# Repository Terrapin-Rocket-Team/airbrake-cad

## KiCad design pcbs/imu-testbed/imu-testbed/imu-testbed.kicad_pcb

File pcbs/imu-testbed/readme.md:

# IMU Testbed
This pcb was created with the goal of allowing us to test & validate different configurations for IMU's and barometers. It currently holds 2 LSM9DSLTR 9-axis IMUs and 1 LPS22HB barometer, and is controlled by a Teensy 4.1. On the back of the pcb are solder jumpers for configuring the address of the accelerometer, gyroscope, and magnitometer for each IMU. On the front are 2 more solder jumpers which allow for controlling the state of the DEN_A/G pin on both IMUs, to either set it floating, high, or low.

## Bill of Materials
- Teensy 4.1 (1x)
- 10uF Capacitor 0805 (4x)
- 100nF Capacitor 0805 (5x)
- [Schottky Diode](https://www.digikey.com/en/products/detail/micro-commercial-co/SMD110PL-TP/2698532) (1x)
- JST connector (2x)
- 1.2k Resistor 0805 (1x)
- 4.4k Resistor 0805 (1x)
- [LSM9DS1TR](https://www.digikey.com/en/products/detail/stmicroelectronics/LSM9DS1TR/4988083?s=N4IgTCBcDaIDIGUCyBOAIggjCAugXyA) (2x)
- [LPS22HB](https://www.digikey.com/en/products/detail/stmicroelectronics/LPS22HBTR/5799910?s=N4IgTCBcDaIDIAUDKYwAkBCIC6BfIA) (1x)
- [Buzzer](https://www.adafruit.com/product/160) (1x)

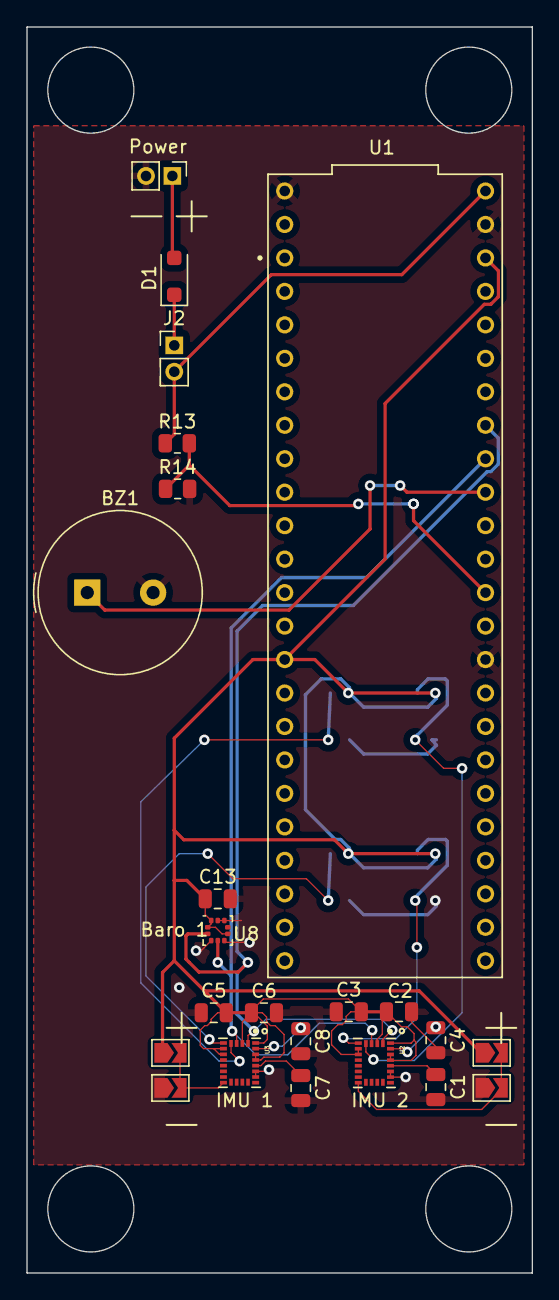
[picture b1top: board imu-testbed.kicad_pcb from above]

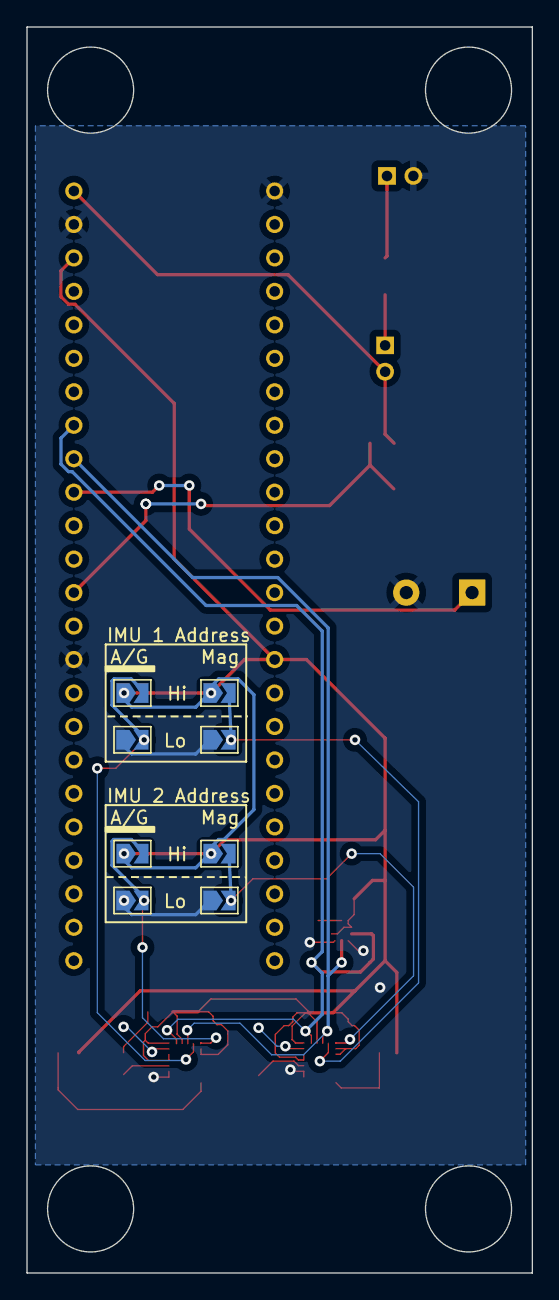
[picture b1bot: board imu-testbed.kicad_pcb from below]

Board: 2 copper layers, 38.4 x 94.6 mm, 31 parts (8 on the bottom side), 19 nets.

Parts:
BZ1: Buzzer; Buzzer_TDK_PS1240P02BT_D12.2mm_H6.5mm
C1, C7: 10nF; C_0805_2012Metric
C2, C6: 10uF; C_0805_2012Metric
C3, C4, C5, C8, C13: 100nF; C_0805_2012Metric
D1: D_Schottky; D_SOD-123F
J1: Battery Connector; PinHeader_1x02_P2.00mm_Vertical
J2: Conn_01x02; PinHeader_1x02_P2.00mm_Vertical
R1, R2, R3, R4, R5, R6, R7, R8, R9, R10, R11, R12: 0 ohm; SolderJumper-2_P1.3mm_Open_TrianglePad1.0x1.5mm
R13: 1.2k; R_0805_2012Metric
R14: 4.4k; R_0805_2012Metric
U1: DEV-16771; MODULE_DEV-16771
U2, U3: LSM9DS1TR; PQFN43P300X350X102-24N
U8: LPS22HB; ST_HLGA-10_2x2mm_P0.5mm_LayoutBorder3x2y

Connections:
+3V3: C2.2, C3.2, C5.2, C6.2, C13.1, R1.1, R2.1, R5.1, R7.1, R9.1, R11.1, U1.3.3V_1 (3.3V), U1.3.3V_2 (3.3V), U2.1 (VDDIO), U2.3 (VDDIO), U2.7 (CS_A/G), U2.8 (CS_M), U2.22 (VDD), U2.23 (VDD), U3.1 (VDDIO), U3.3 (VDDIO), U3.7 (CS_A/G), U3.8 (CS_M), U3.22 (VDD), U3.23 (VDD), U8.1 (Vdd_IO), U8.6 (~CS), U8.10 (VDD)
/BATT_IN: D1.1 (K), J2.1
/Barometric pressure sensor/SCL: U1.19 (A5), U2.2 (SCL/SPC), U3.2 (SCL/SPC), U8.2 (SCL)
/Barometric pressure sensor/SDA: U1.18 (A4), U2.4 (SDA/SDI/SDO), U3.4 (SDA/SDI/SDO), U8.4 (SDA)
/Teensy 4.1/1s lipo analog voltage splitter/V_SCALED: R13.2, R14.1, U1.14 (A0)
/Teensy 4.1/BUZZ: BZ1.1 (-), U1.17 (A3)
/Teensy 4.1/VIN: J2.2, R13.1, U1.VIN
GND: BZ1.2 (+), C1.2, C2.1, C3.1, C4.2, C5.1, C6.1, C7.2, C8.2, C13.2, J1.2, R3.1, R4.1, R6.1, R8.1, R10.1, R12.1, R14.2, U1.GND1 (GND), U1.GND2 (GND), U1.GND3 (GND), U2.19 (GND), U2.20 (GND), U3.19 (GND), U3.20 (GND), U8.3 (RES), U8.5 (SA0), U8.8 (GND), U8.9 (GND)
unnamed: D1.2 (A), J1.1
unnamed: C4.1, U2.24 (C1)
unnamed: C1.1, U2.21 (CAP)
unnamed: R9.2, R10.2, U2.13 (DEN_A/G)
unnamed: R1.2, R3.2, U2.5 (SDO_A/G)
unnamed: R5.2, R6.2, U2.6 (SDO_M)
unnamed: C8.1, U3.24 (C1)
unnamed: C7.1, U3.21 (CAP)
unnamed: R11.2, R12.2, U3.13 (DEN_A/G)
unnamed: R2.2, R4.2, U3.5 (SDO_A/G)
unnamed: R7.2, R8.2, U3.6 (SDO_M)

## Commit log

2023-08-02 Designed pcb, wrote readme, produced gerbers
